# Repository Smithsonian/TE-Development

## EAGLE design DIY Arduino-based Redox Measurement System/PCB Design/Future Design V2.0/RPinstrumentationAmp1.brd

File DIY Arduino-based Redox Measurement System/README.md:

# **Arduino-Based Redox Measurement System**

Welcome to the repository for our **Arduino-Based Redox Measurement System**—a cost-effective, DIY solution for high-accuracy redox potential measurements in soil and marsh environments. This repository is your one-stop resource for replicating, modifying, and enhancing the system for your research or field applications.

---

## **🔍 Overview**
This project is designed to measure and log redox potential in soil using an Arduino-based setup. The system is ideal for environmental researchers, soil scientists, and anyone interested in real-time, low-cost data acquisition for redox potential studies.

---

## **🚀 Features**
- **Autonomous Operation**: Fully automated data collection with minimal user intervention.
- **High Precision**: ±500 mV data acquisition range every 5 seconds.
- **Multi-Channel Input**: Supports multiple probes for simultaneous measurements.
- **Built-in Diagnostics**: Power-up self-test and automatic calibration for reliable performance.
- **Remote Ready**: Compatible with battery and solar-powered setups for off-grid deployments.
- **User-Friendly Interface**: Real-time data display via LCD and seamless data logging to an SD card.
- **Expandable**: Easily upgradeable to include remote monitoring and additional channels.

---

## **📁 Repository Contents**
- **`/Arduino Code`**: All Arduino sketches for configuring the redox system.
- **`/PCB Designs`**: Custom PCB layouts for integrating all components into a single board.
- **`/Parts List`**: Comprehensive list of materials required to build the system.
- **`/R Scripts`**: Redox Measurement Data processing scripts for analyzing logged data.
- **`/Documentations`**: Detailed guides, wiring diagrams, and setup instructions.

---

## **📈 Applications**
- **Soil Health Monitoring**: Assess microbial activity, nutrient cycling, and carbon flux.
- **Environmental Research**: Study redox potential dynamics in wetlands and marshes.
- **Field Deployments**: Use in remote locations with solar-powered configurations.

---

## **🎯 Future Scope**
- Integrate **XBee modules** for remote data logging.
- Expand input capability from 3 to 6 channels.
- Validate new designs with field trials.
- Optimize PCBs for mass production and release a final design.

---

## **📧 Contribute or Collaborate**
We’re open to contributions! Submit pull requests or raise issues to enhance the system. For collaboration inquiries, contact us at **[hiremuttt@si.edu] [westbrooke@si.edu]**.

---

## **❤️ Acknowledgments**
This project wouldn’t have been possible without the contributions from our team and the funding for this project provided by the DOE Environmental System Science Program and the Smithsonaian Institution. 
A huge SHOUTOUT and THANK YOU to the Smithsonian Environmental Research Center and the Technology and Ecology Lab. 

---

**Let’s make field research smarter, affordable, and accessible for everyone!**  
_Star ⭐ the repo if you find it useful._  

---

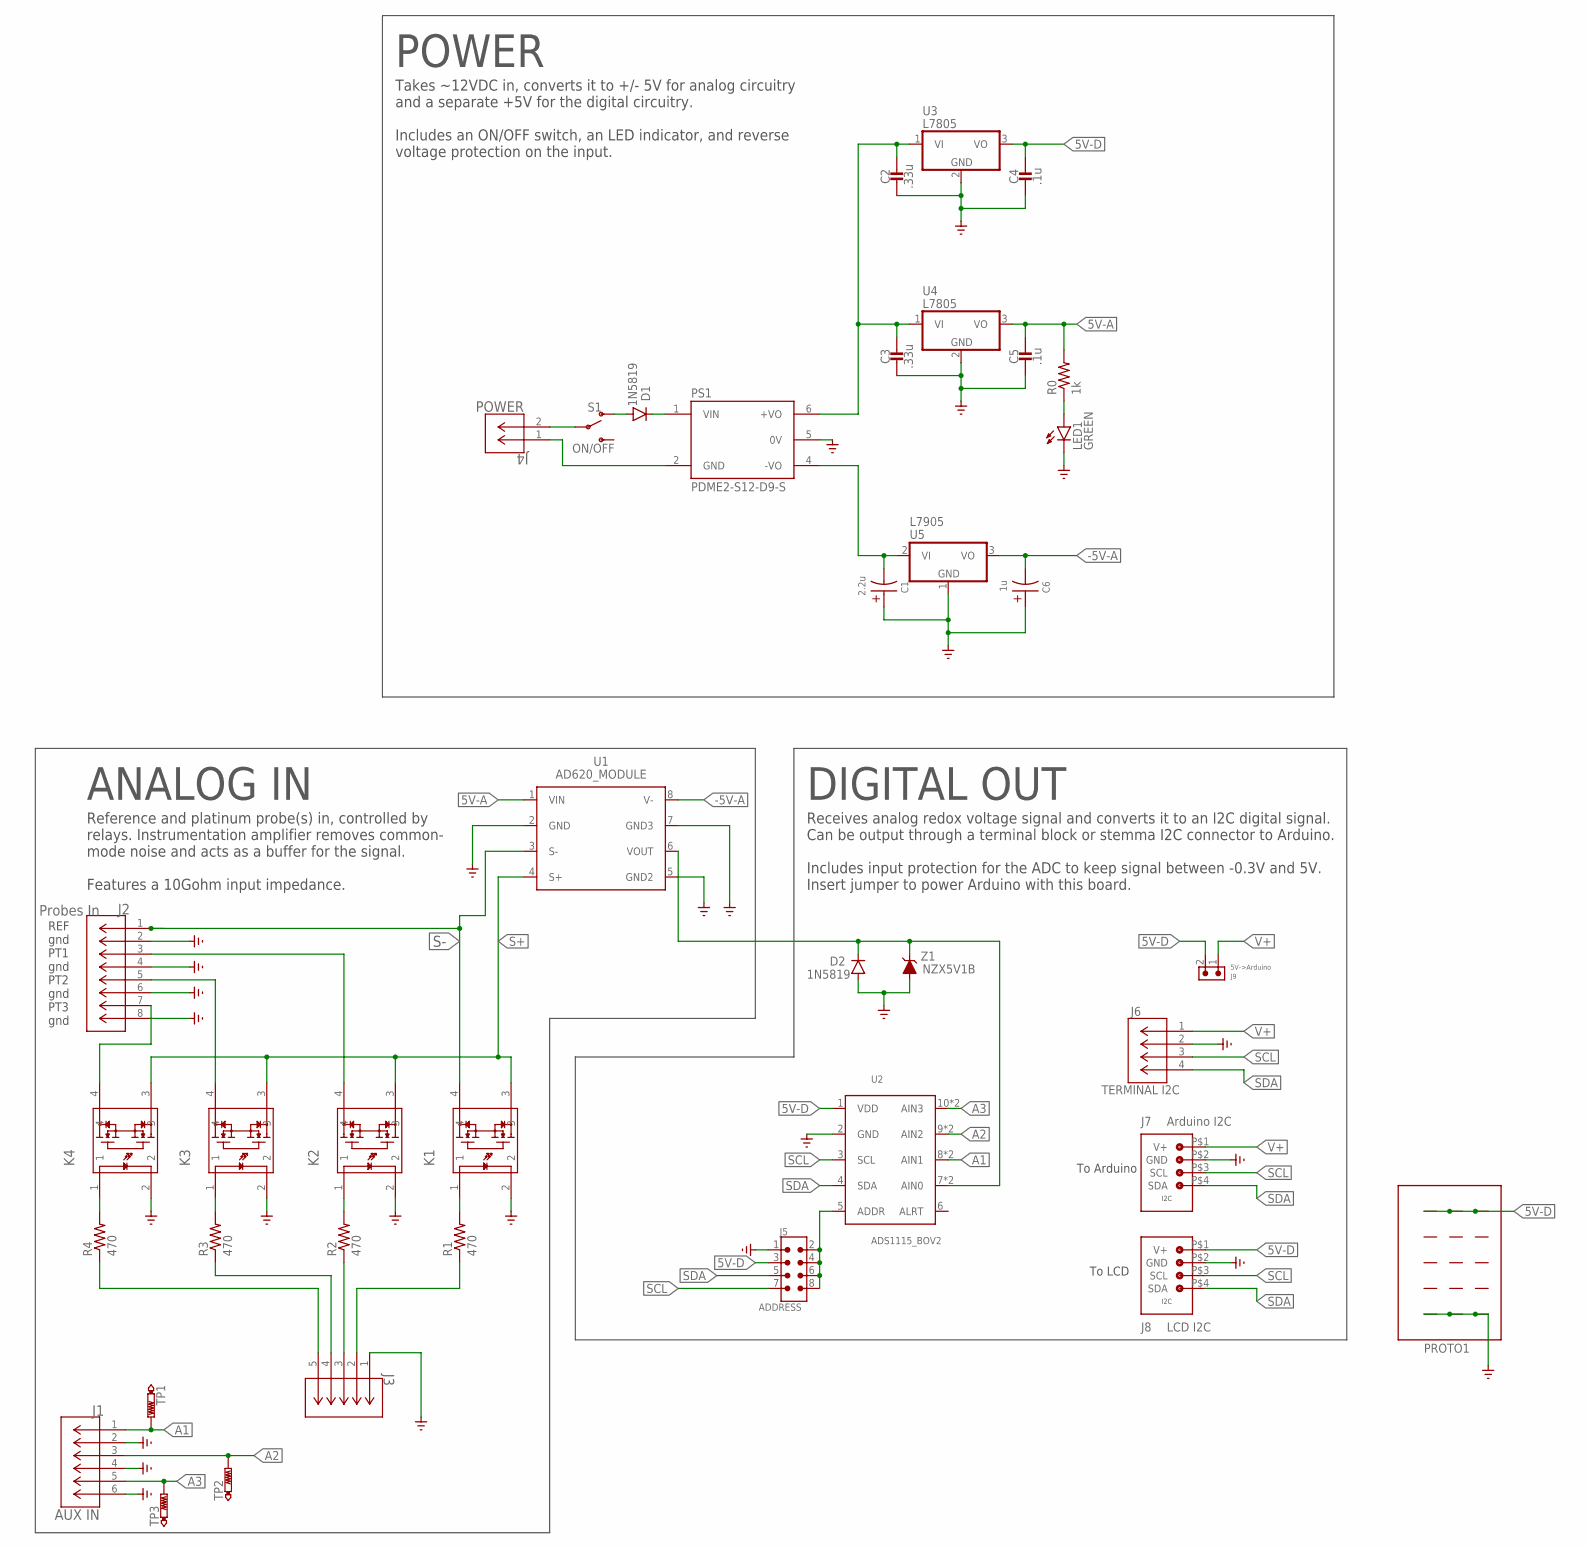
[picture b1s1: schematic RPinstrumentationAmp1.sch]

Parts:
C1: 2.2u; E2,5-5
C2, C3: .33u; THCAPCERAMIC
C4, C5: .1u; THCAPCERAMIC
C6: 1u; E2,5-5
D1, D2: 1N5819; DIODE-TH
J1: AUX IN; 6PIN_TERMINAL_5MM
J2: Probes In; 8PIN_TERMINAL_5MM
J3: 5PIN_TERMINAL_5MM
J4: POWER; CONN2_710002_WRE
J5: ADDRESS; 61300821121
J6: TERMINAL I2C; 4PIN_TERMINAL_5MM
J7: Arduino I2C; JST_PH_4PIN
J8: LCD I2C; JST_PH_4PIN
J9: 5V->Arduino; 61300211121
K1, K2, K3, K4: G3VM-61A1A-DIP4_THD_OMR; A-DIP4_THD_OMR
LED1: GREEN; LED-5MM-TH
PROTO1: PROTO_AREA_5X3
PS1: PDME2-S12-D9-S; CONV_PDME2-S12-D9-S
R0: 1k; THRESISTOR
R1, R2, R3, R4: 470; THRESISTOR
S1: ON/OFF; TT11_SPDT
TP1, TP2, TP3: PTR1PAD1-13; P1-13
U1: AD620_MODULE
U2: ADS1115_BOV2; ADS1115_V2
U3, U4: L7805; TO220V
U5: L7905; TO220V
Z1: NZX5V1B; DIODE-TH

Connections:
5V-A: C5.C1 (1), R0.R2 (2), U1.1 (VIN), U4.3 (VO)
5V-D: C4.C1 (1), J5.3, J8.P$1 (V+), J9.2, PROTO1.1, PROTO1.2, PROTO1.3, U2.1 (VDD), U3.3 (VO)
-5V-A: C6.-, U1.8 (V-), U5.3 (VO)
A1: J1.1, TP1.TP, U2.8 (AIN1), U2.A1 (AIN1)
A2: J1.3, TP2.TP, U2.9 (AIN2), U2.A2 (AIN2)
A3: J1.5, TP3.TP, U2.10 (AIN3), U2.A3 (AIN3)
GND: C1.+, C2.C2 (2), C3.C2 (2), C4.C2 (2), C5.C2 (2), C6.+, D2.P$1 (A), J1.2, J1.4, J1.6, J2.2, J2.4, J2.6, J2.8, J3.1, J5.1, J6.2, J7.P$2 (GND), J8.P$2 (GND), K1.2, K2.2, K3.2, K4.2, LED1.K (C), PROTO1.13, PROTO1.14, PROTO1.15, PS1.5 (0V), U1.2 (GND), U1.5 (GND2), U1.7 (GND3), U2.2 (GND), U3.2 (GND), U4.2 (GND), U5.1 (GND), Z1.P$1 (A)
unnamed: D2.P$2 (C), U1.6 (VOUT), U2.7 (AIN0), U2.A0 (AIN0), Z1.P$2 (C)
unnamed: C1.-, PS1.4 (-VO), U5.2 (VI)
unnamed: D1.P$2 (C), PS1.1 (VIN)
unnamed: J4.1, PS1.2 (GND)
unnamed: J2.7, K4.4
unnamed: J2.5, K3.4
unnamed: C2.C1 (1), C3.C1 (1), PS1.6 (+VO), U3.1 (VI), U4.1 (VI)
unnamed: J4.2, S1.P$2 (C)
unnamed: LED1.A, R0.R1 (1)
unnamed: D1.P$1 (A), S1.P$1 (1)
unnamed: J2.3, K2.4
unnamed: K4.1, R4.R2 (2)
unnamed: J5.2, J5.4, J5.6, J5.8, U2.5 (ADDR)
unnamed: J3.5, R4.R1 (1)
unnamed: K3.1, R3.R2 (2)
unnamed: J3.4, R3.R1 (1)
unnamed: K2.1, R2.R2 (2)
unnamed: J3.3, R2.R1 (1)
unnamed: J3.2, R1.R1 (1)
unnamed: K1.1, R1.R2 (2)
S+: K1.3, K2.3, K3.3, K4.3, U1.4 (S+)
S-: J2.1, K1.4, U1.3 (S-)
SCL: J5.7, J6.3, J7.P$3 (SCL), J8.P$3 (SCL), U2.3 (SCL)
SDA: J5.5, J6.4, J7.P$4 (SDA), J8.P$4 (SDA), U2.4 (SDA)
V+: J6.1, J7.P$1 (V+), J9.1

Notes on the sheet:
POWER
ANALOG IN
DIGITAL OUT
Takes ~12VDC in, converts it to +/- 5V for analog circuitry and a separate +5V for the digital circuitry. Includes an ON/OFF switch, an LED indicator, and reverse voltage protection on the input.
Receives analog redox voltage signal and converts it to an I2C digital signal. Can be output through a terminal block or stemma I2C connector to Arduino. Includes input protection for the ADC to keep signal between -0.3V and 5V. Insert jumper to power Arduino with this board.
Reference and platinum probe(s) in, controlled by relays. Instrumentation amplifier removes common- mode noise and acts as a buffer for the signal. Features a 10Gohm input impedance.
REF gnd PT1 gnd PT2 gnd PT3 gnd
To Arduino
To LCD

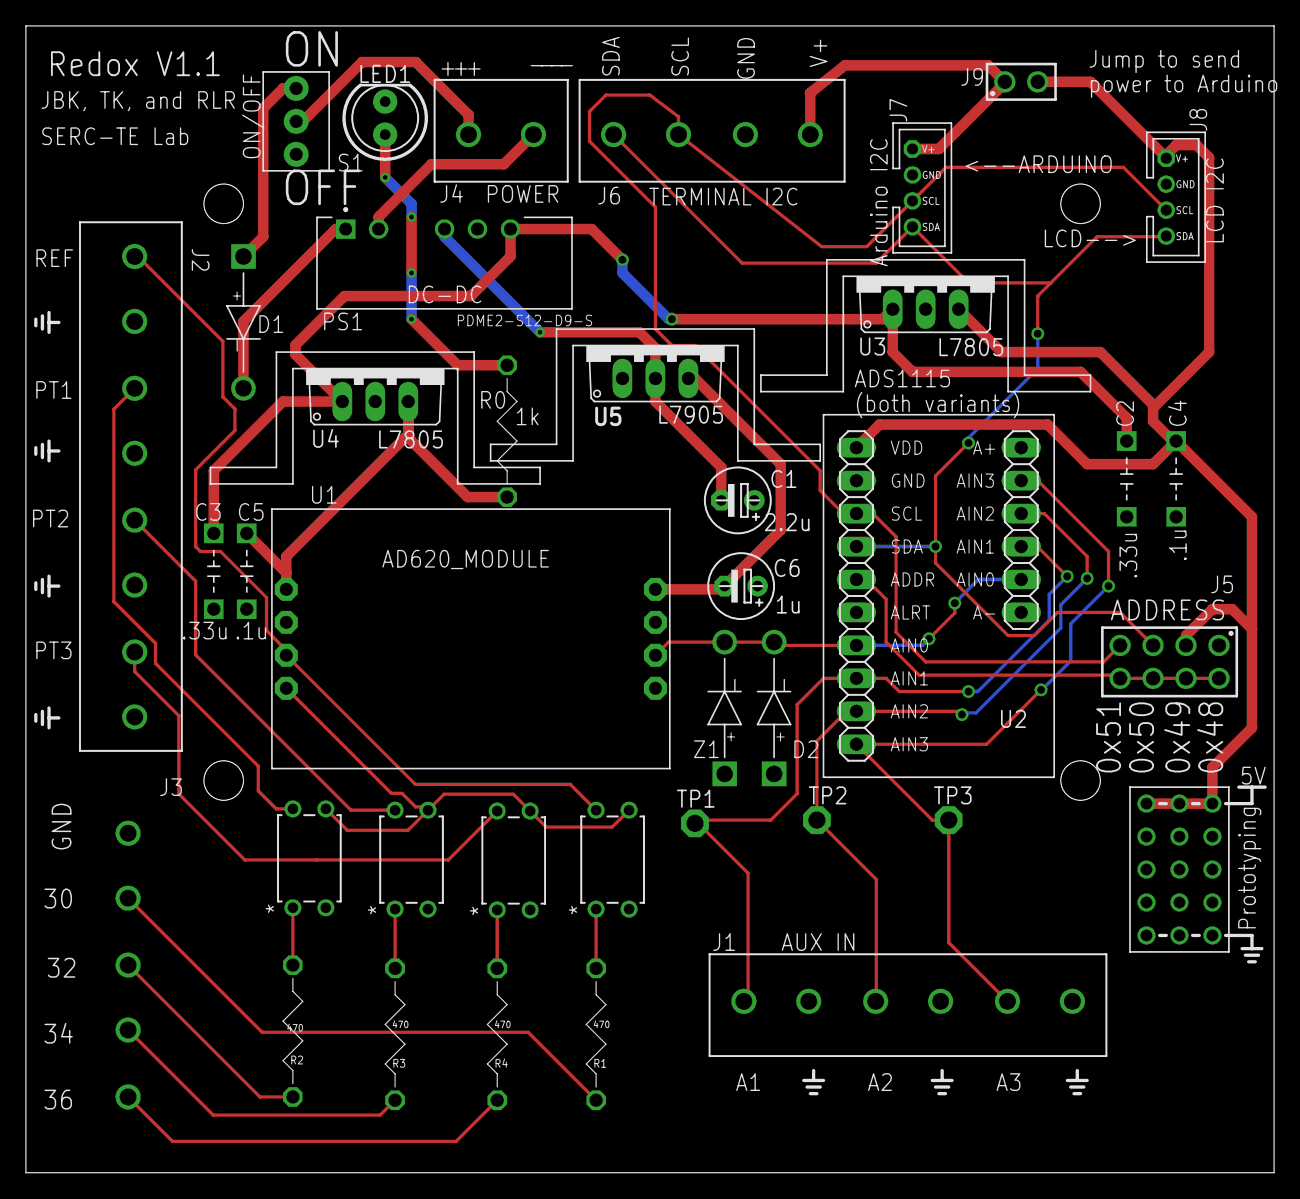
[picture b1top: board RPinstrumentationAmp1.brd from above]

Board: 2 copper layers, 96.2 x 88.4 mm, 39 parts (1 on the bottom side), 32 nets.

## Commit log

2024-12-04 Create DIY Arduino-based Redox Measurement System
2024-12-04 Create PCB Design
    The Printed Circuit Board (PCB) Schematic Design and Layout

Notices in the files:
parts and their libraries:
Wurth_Connectors_WR-PHD: Copyright: Würth Elektronik
COPYRIGHT: Copyright (C) 2023 Ultra Librarian. All rights reserved.
COPYRIGHT: Copyright (C) 2024 Ultra Librarian. All rights reserved.
